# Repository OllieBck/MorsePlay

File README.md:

# MorsePlay

MorsePlay uses the [Morse GBoard](https://support.google.com/accessibility/android/answer/9011881) on Android devices to activate switch adapted toys and similar interfaces via a pluggable Bluetooth Low Energy (BLE) module.

It is developed by the [Adaptive Design Association](http://www.adaptivedesign.org/) and [NottLimited](http://www.tandemmaster.org/home.html).

To see a demo of the project, visit https://youtu.be/Mf9dzT8w3vc.

To see more about switch adapting mass produced toys, visit [DIYAbility.org](https://www.diyability.org/guide/switch-adapting-a-remote-control-toy/) as well as [GoBabyGo Cars](https://www.diyability.org/2014/11/go-baby-go-the-ultimate-toy-hack/) -- or to find out more about [GoBabyGo](https://sites.udel.edu/gobabygo/).

The project comes in 3 parts on this repo.

["MorsePlay -- App"](https://github.com/OllieBck/MorsePlay/tree/master/MorsePlay--App) modifies an example from Don Coleman's [Cordova BLE Central Library](https://github.com/don/cordova-plugin-ble-central).

["MorsePlay -- BLE_Module"](https://github.com/OllieBck/MorsePlay/tree/master/MorsePlay--BLE_Module) utilizes a RedBear Labs BLE Nano V2 and is built off an [example](https://github.com/RedBearLab/arduino-BLEPeripheral/tree/master/examples/SimpleChat) the lab created of Sandeep Mistry's [Arduino BLE Peripheral](https://github.com/sandeepmistry/arduino-BLEPeripheral) library.

["MorsePlay -- Schematics"](https://github.com/OllieBck/MorsePlay/tree/master/MorsePlay%20-%20Schematics) include the Eagle files for the simple circuit for the BLE module relay board.

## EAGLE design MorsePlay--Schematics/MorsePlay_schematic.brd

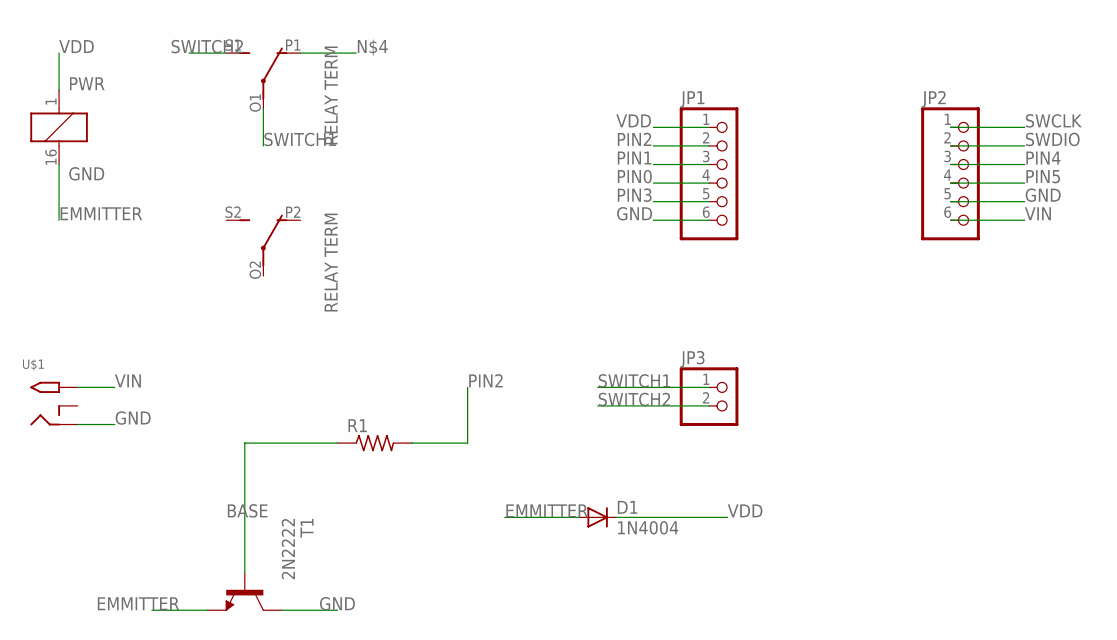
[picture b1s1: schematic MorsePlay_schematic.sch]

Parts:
D1: 1N4004; DO41-10
JP1, JP2: PINHD-1X6; 1X06
JP3: PINHD-1X2; 1X02
R1: R-US_0204/7; 0204/7
RELAY1: RELAY_3VTERMINAL; 351
T1: 2N2222; TO92-EBC-OVAL
U$1: DCPOWERJACK; DCJACK_2MM_PTH

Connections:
BASE: R1.1, T1.B
EMMITTER: D1.A, RELAY1.16 (GND), T1.E
GND: JP1.6, JP2.5, T1.C, U$1.GND (RING)
PIN0: JP1.4
PIN1: JP1.3
PIN2: JP1.2, R1.2
PIN3: JP1.5
PIN4: JP2.3
PIN5: JP2.4
SWCLK: JP2.1
SWDIO: JP2.2
SWITCH1: JP3.1, RELAY1.O1 (COM)
SWITCH2: JP3.2, RELAY1.S1 (NO)
VDD: D1.C, JP1.1, RELAY1.1 (PWR)
VIN: JP2.6, U$1.PWR (TIP)

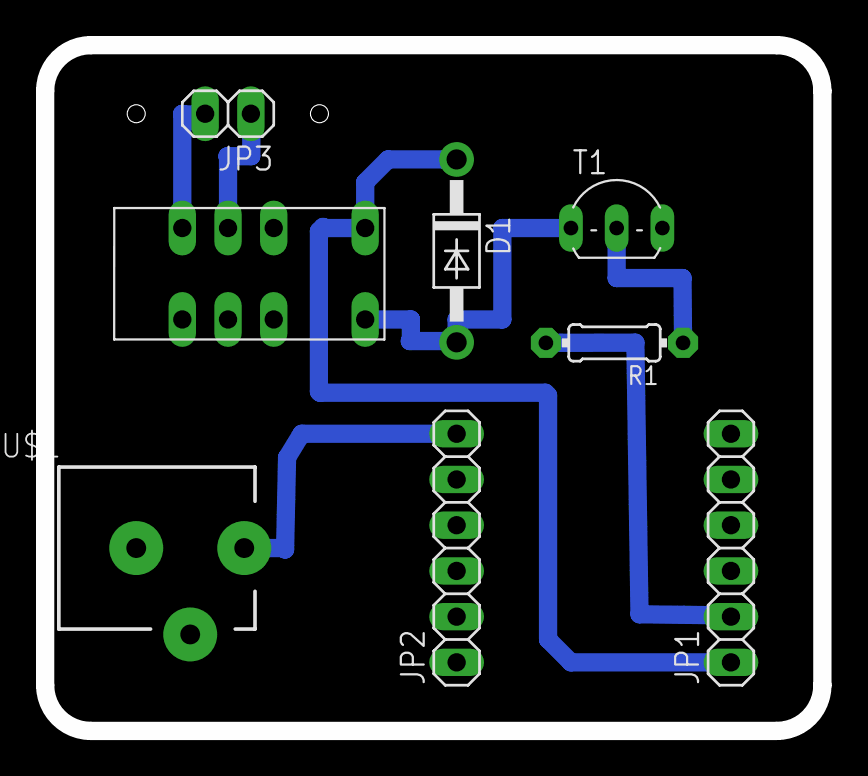
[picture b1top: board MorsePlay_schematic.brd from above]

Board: 2 copper layers, 43.2 x 38.1 mm, 8 parts (0 on the bottom side), 8 nets.

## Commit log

2018-05-30 add references to readme
2018-05-31 add README sections
2018-05-31 updates website addresses
2018-05-31 fix link
